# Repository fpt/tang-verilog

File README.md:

# tang-verilog

Tang Nano 20K (Gowin GW2AR-18) と RP2350 で、レトロゲーム機の VDP のようなものを作るためのプロジェクトです。

- FPGA 側 (Tang Nano 20K): VDP 本体。今は HDMI (DVI) に 640x480@60Hz の映像を出す
- RP2350 側: ホスト CPU 役。SPI などで VDP にコマンドを送る (予定)

ツールはすべてオープンソースのものを Docker コンテナ内で動かします。ホストに必要なのは Docker と make だけです
(ボードへの書き込みだけは例外です。下の「書き込み」を参照)。

## ドキュメント

- [docs/SPECIFICATION.md](docs/SPECIFICATION.md): アプリケーション開発者向けの仕様 (接続、レジスタ、コマンド、データ形式、タイミング、制限)
- [docs/ARCHITECTURE.md](docs/ARCHITECTURE.md): 設計方針と今の実装 (レジスタバス、レジスタマップ、クロック、SDRAM)
- [docs/GPU_PLAN.md](docs/GPU_PLAN.md): SDRAM フレームバッファの tiny-GPU の開発計画 (ハーネスで検証しながら進める)
- [docs/WIRING.md](docs/WIRING.md): RP2350 と Tang Nano 20K の配線・SPI ピン割り当て
- [docs/DEVELOPMENT.md](docs/DEVELOPMENT.md): 開発環境の補足

## 状態

- 実機 (Tang Nano 20K + HDMI) で、SPI のハーネス (RP2040-Zero) からコマンド GPU (図形・BLIT)、ライン合成、タイル レイヤが動いている。
  すべて 参照モデル = Verilator = 実機 の CRC で確かめている ([docs/HARNESS.md](docs/HARNESS.md))
- 進み具合: コマンド GPU は [docs/GPU_PLAN.md](docs/GPU_PLAN.md) (M0〜M9 済み、M8 はやめた)、エミュレータ向けのタイル/スプライト エンジンは
  [docs/EMU_GPU_PLAN.md](docs/EMU_GPU_PLAN.md) (E1〜E4・E7 (Mode 7 と霧) 済み、次は E5 のホスト翻訳層)、
  [rs-kessel](https://github.com/fpt/rs-kessel) を載せる準備は [docs/KESSEL_ON_VDP.md](docs/KESSEL_ON_VDP.md) (K1〜K4 の VDP 側 = 8bpp の面・BLIT4・スプライトのセル順とバンク・STRETCH_BLIT・ライトマップ済み)
- 3D GPU (タイルベース、VDP を外した別のビットストリーム `make bitstream-gpu3d`。フラッシュに VDP と一緒に置き、`RECONFIG` で入れ替える) は [docs/GPU3D_PLAN.md](docs/GPU3D_PLAN.md) (G0 の骨格、G1 の三角形 (単色・Gouraud・Z)、G2 のタイルベースの遅延描画 (TBDR)、G3 のテクスチャ、G4 の半透明、G5 の場面 (ロゴ・トンネル・映り込む玉の部屋・夜の街、`harness.py demo <場面>`) 済み)
- 本番ホスト (RP2350) とのリンクは HSTX に決めた (EMU_GPU_PLAN.md の「本番のリンク」)。まだ作っていない

## ツール

| 用途 | ツール | 入手元 |
| --- | --- | --- |
| 論理合成 | Yosys + yosys-slang プラグイン (SystemVerilog フロントエンド) | [OSS CAD Suite](https://github.com/YosysHQ/oss-cad-suite-build) |
| 配置配線 | nextpnr-himbaechel (Gowin) | 同上 |
| ビットストリーム生成 | apicula (`gowin_pack`) | 同上 |
| シミュレーション | Icarus Verilog / Verilator / cocotb | 同上 |
| 書き込み | openFPGALoader | 同上 (ただしコンテナからは USB が使えない) |
| RP2350 ファームウェア | arm-none-eabi-gcc + pico-sdk 2.3.1 + picotool | Debian パッケージ / GitHub |

## セットアップ

```bash
make images
```

`docker/fpga` と `docker/pico` の 2 つのイメージを順番にビルドします (`make image-fpga` / `make image-pico` で個別にも可)。
FPGA 側は OSS CAD Suite (約 1GB) をダウンロードするので時間がかかります。
開発環境についての補足は [docs/DEVELOPMENT.md](docs/DEVELOPMENT.md) を参照してください。

### メモリについて

Docker Desktop の割り当てメモリが少ないと、イメージのビルド (特に picotool のコンパイル) でメモリが足りなくなることがあります。
2 つのイメージは並列ではなく 1 つずつビルドしてください。

## 使い方

```bash
make help
```

| コマンド | 内容 |
| --- | --- |
| `make lint` | Verilator で RTL を lint |
| `make sim` | `sim/tb_*.sv` を全部実行 (`SIM=verilator` で Verilator を使う)。VCD は `build/sim/` に出力 |
| `make sim-tb_tmds_encoder` | テストベンチを 1 つだけ実行 |
| `make render` | Verilator で映像出力を回し、各フレームを `build/render/frame_*.png` に保存 |
| `make bitstream` | 合成 → 配置配線 → VDP (`build/vdp/top.fs`) と 3D GPU (`build/gpu3d/top.fs`)。1 つだけなら `make bitstream-vdp` / `bitstream-gpu3d` |
| `make flash` | VDP をフラッシュの 0x000000、3D GPU を 0x100000 に (電源を入れると VDP。`harness.py reconfig` か、要るときに `harness.py` が自分で入れ替える) |
| `make prog` / `make prog-3d` | VDP / 3D GPU を SRAM に (開発中の確かめ) |
| `make bitstream-lcd` | 40 ピン RGB LCD (800x480) に HDMI と同じテストパターンを出す → `build/lcd/top_lcd.fs` (`make prog-lcd` で書き込み) |
| `make scenario SCENARIO=scenarios/m5_basic.json` | GPU のシナリオをシステム全体の RTL (Verilator) で走らせ、参照モデルの CRC と比べる。実機は `harness.py scenario` |
| `make render FREEZE=1` | アニメーションを止めた参照画像と各フレームの CRC (`frames.json`) を `build/render_frozen/` に (実機の `FRAME_CRC` と比べる) |
| `make render-lcd` | LCD 版の映像を `build/render_lcd/frame_*.png` に保存 |
| `make harness-fw` / `python3 tools/harness/harness.py <cmd>` | ハーネスの RP2 ブリッジとホストツール (`status` / `selftest` / `memtest` / `frametest` / `fbtest` / `prog` など)。詳細は [docs/HARNESS.md](docs/HARNESS.md) |
| `make prog` / `make flash` | Tang Nano 20K の SRAM / Flash に書き込み (書く前に、ハーネスのピンと衝突しないかを `pincheck-<設計>` が自動で検査する) |
| `make fw` | RP2350 ファームウェアをビルド (`firmware/build/vdp_host.uf2`) |
| `make shell` / `make shell-pico` | 各コンテナのシェルに入る |
| `make zip` | 別環境へ持っていくためのソース一式を `dist/<ディレクトリ名>.zip` に作成 (ホストの git と zip を使用) |

### 波形を見る

GTKWave は GUI ツールなので、macOS 上の Docker からは簡単には開けません。ローカルに何も入れずに見るなら
[Surfer のブラウザ版](https://app.surfer-project.org/) で `build/sim/*.vcd` を開いてください。

### 書き込み

macOS 上の Docker Desktop のコンテナからは USB デバイスにアクセスできないため、`make prog` だけはホストの `openFPGALoader` を使います。

```bash
brew install openfpgaloader
```

ホストに何も入れたくない場合は、Gowin 公式の Programmer を使う方法もあります。

RP2350 は BOOTSEL ボタンを押しながら USB 接続し、出てきたドライブに `firmware/build/vdp_host.uf2` をコピーすれば書き込めます (ツール不要)。
ボードを変えるときは `make fw PICO_BOARD=<ボード名>`、RISC-V コア (Hazard3) を使うときは `make fw PICO_PLATFORM=rp2350-riscv` です。

## ディレクトリ構成

```
docker/
  fpga/Dockerfile        FPGA ツール (OSS CAD Suite)
  pico/Dockerfile        RP2350 ツール (pico-sdk, picotool)
rtl/
  vdp/                   ベンダ非依存の RTL (シミュレーション可能)
    video_timing.sv      640x480@60Hz のタイミング生成
    vdp_core.sv          VDP コアの雛形 (カラーバー + 市松模様 + 跳ね回る四角)
    tmds_encoder.sv      DVI の TMDS エンコーダ
    vdp_video.sv         タイミング + コアをまとめたもの (MODE 0: 640x480 HDMI / 1: 800x480 LCD)
  gowin/                 Gowin のプリミティブを使う部分
    dvi_tx.sv            OSER10 + TLVDS_OBUF による DVI 送信
    top.sv               トップ (rPLL 126MHz → CLKDIV /5 → 25.2MHz)
    top_lcd.sv           RGB LCD 版トップ (rPLL 33MHz、800x480)
    blackbox/            Gowin プリミティブのブラックボックス定義 (合成専用)
constraints/
  tangnano20k.cst        ピン配置 (HDMI)
  tangnano20k_lcd.cst    ピン配置 (40 ピン RGB LCD)
sim/
  tb_*.sv                テストベンチ (Icarus Verilog / Verilator)
  verilator/render_main.cpp  フレームを画像に書き出すシミュレータ
firmware/                RP2350 ファームウェア (pico-sdk)
scripts/
  ppm2png.py             PPM → PNG 変換
```

## ハードウェアメモ (Tang Nano 20K)

| 信号 | ピン |
| --- | --- |
| 27MHz クロック | 4 |
| ボタン S1 / S2 (押下で 1) | 88 / 87 |
| LED0〜5 (負論理) | 15〜20 |
| HDMI CLK / D0 / D1 / D2 (P,N) | 33,34 / 35,36 / 37,38 / 39,40 |

- デバイス: `GW2AR-LV18QN88C8/I7` (nextpnr の family は `GW2A-18C`)
- 40 ピン RGB LCD の R/G 信号の一部 (33〜40) は HDMI と同じピンなので、HDMI と LCD は同時には使えません (別の `TARGET`)
- ピクセルクロックは 25.2MHz で、規格値の 25.175MHz からわずかにずれています (たいていのモニタは問題なく表示します)

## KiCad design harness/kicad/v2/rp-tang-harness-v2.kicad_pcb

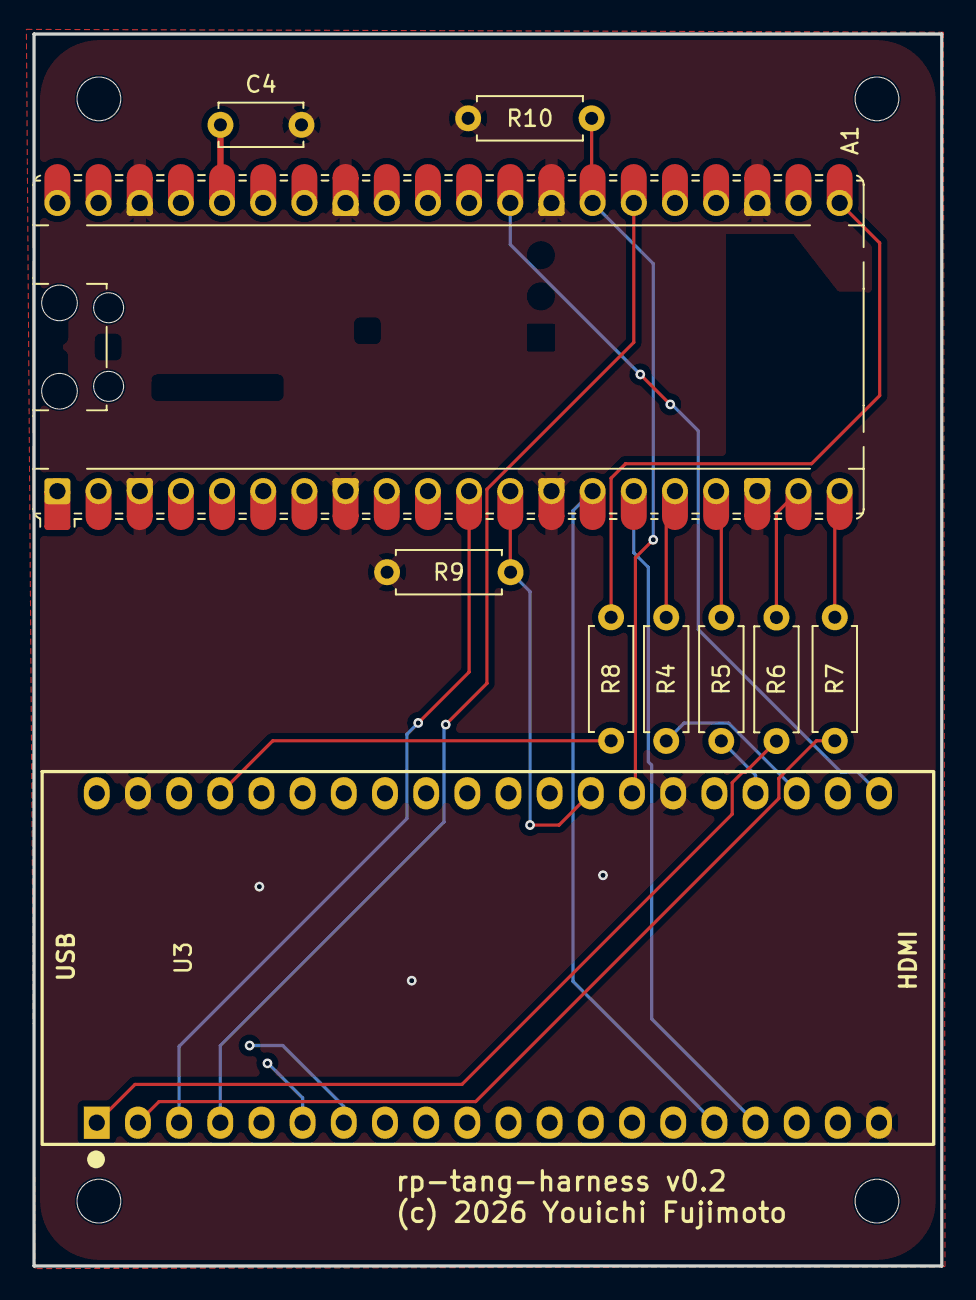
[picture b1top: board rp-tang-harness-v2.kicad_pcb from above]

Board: 2 copper layers, 56.0 x 76.0 mm, 14 parts (0 on the bottom side), 19 nets.

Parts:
A1: RaspberryPi_Pico; RaspberryPi_Pico_Common_Unspecified
C4: 0.1u; C_Disc_D5.0mm_W2.5mm_P5.00mm
H_LL1: MountingHole; MountingHole_2.7mm
H_LR1: MountingHole; MountingHole_2.7mm
H_UL1: MountingHole; MountingHole_2.7mm
H_UR1: MountingHole; MountingHole_2.7mm
R4, R5, R6, R7, R8: 33; R_Axial_DIN0207_L6.3mm_D2.5mm_P7.62mm_Horizontal
R9, R10: 4.7k; R_Axial_DIN0207_L6.3mm_D2.5mm_P7.62mm_Horizontal
U3: Sipeed_Tang_Nano_20K; DIP-40_TangNano20K

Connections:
+3V3: A1.36 (3V3), C4.1
/CIPO: A1.11 (GPIO8), U3.3 (75_IOT34A)
/COPI: A1.15 (GPIO11), U3.17 (19_IOL51A)
/CS: A1.12 (GPIO9), R9.1, U3.28 (86_IOT4A)
/HSTX_CLK: R8.2, U3.37 (80_IOT27A)
/HSTX_CLK_P: A1.21 (GPIO16), R8.1
/HSTX_D0: R4.2, U3.23 (71_IOT44A)
/HSTX_D0_P: A1.16 (GPIO12), R4.1
/HSTX_D1: R5.2, U3.24 (72_IOT40B)
/HSTX_D1_P: A1.17 (GPIO13), R5.1
/HSTX_D2: R6.2, U3.1 (73_IOT40A)
/HSTX_D2_P: A1.19 (GPIO14), R6.1
/HSTX_D3: R7.2, U3.2 (74_IOT34B)
/HSTX_D3_P: A1.20 (GPIO15), R7.1
/IRQ: A1.26 (GPIO20), U3.4 (85_IOT4B)
/RESET: A1.27 (GPIO21), R10.1, U3.27 (79_IOT27B)
/SCK: A1.14 (GPIO10), U3.16 (20_IOL51B)
/VSYNC: A1.29 (GPIO22), U3.21 (52_IOR39A)
GND: A1.3 (GND), A1.8 (GND), A1.13 (GND), A1.18 (GND), A1.23 (GND), A1.28 (GND), A1.33 (AGND), A1.38 (GND), C4.2, R9.2, R10.2, U3.20 (GND), U3.26 (GND), U3.39 (GND)

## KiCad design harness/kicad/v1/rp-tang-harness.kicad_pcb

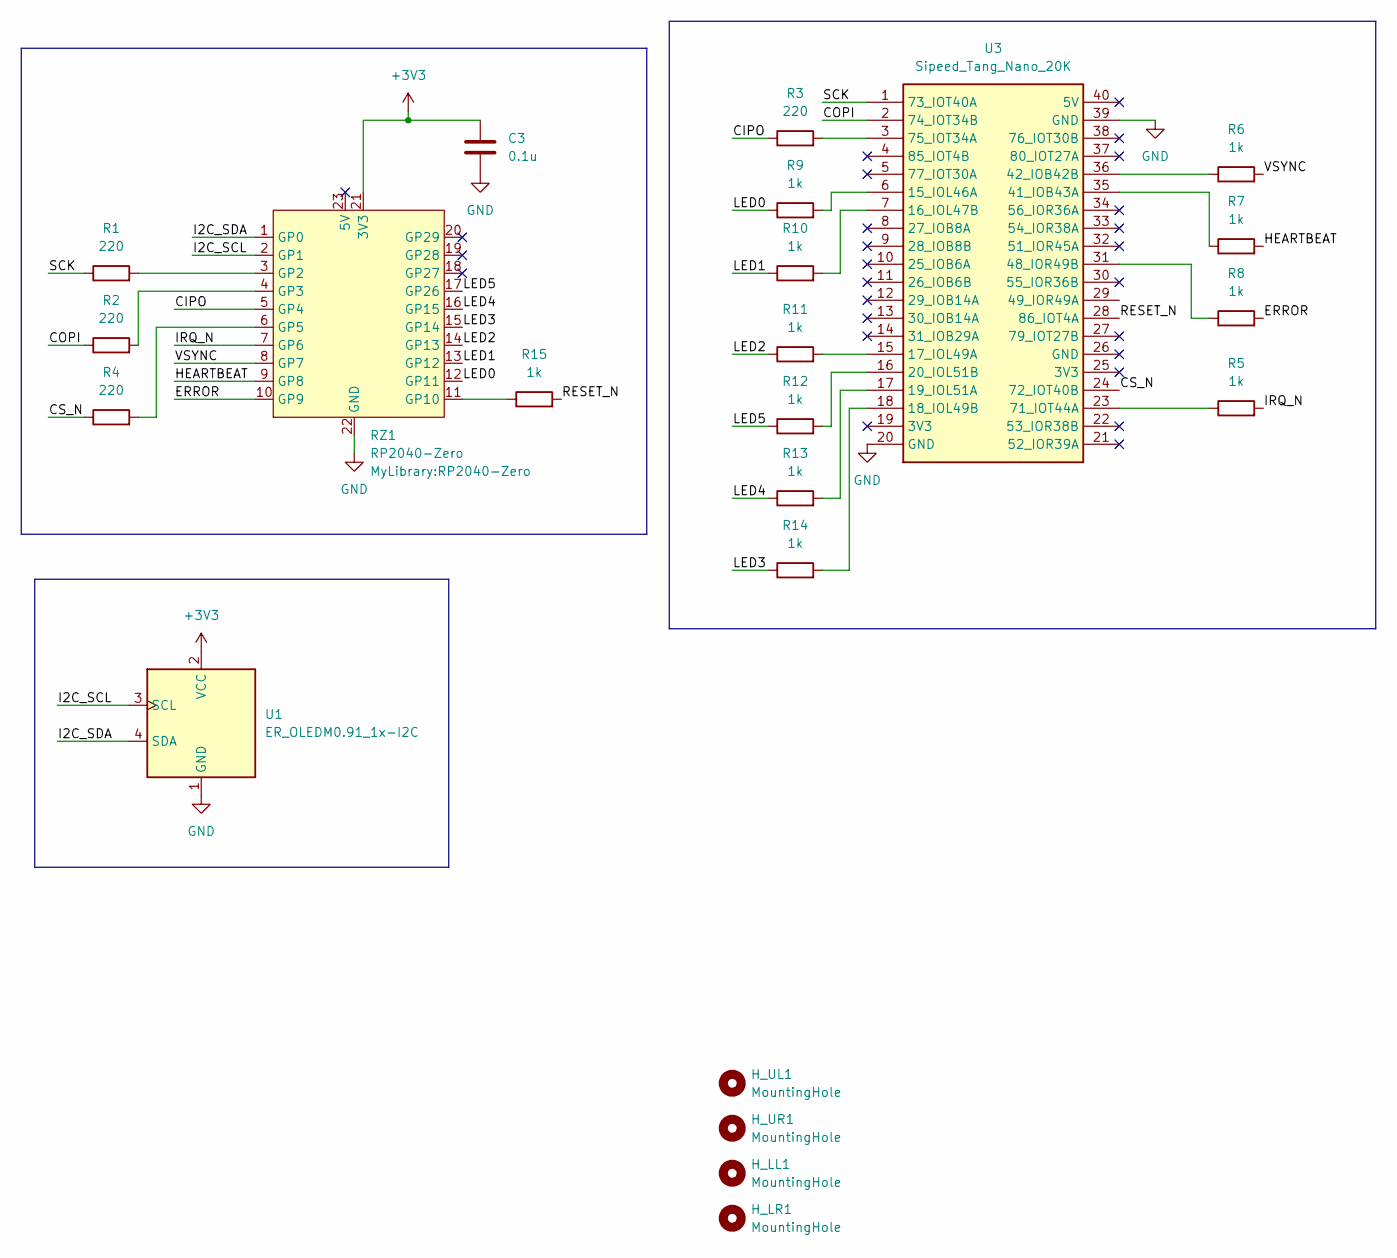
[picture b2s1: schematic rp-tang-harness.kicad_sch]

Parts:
C3: 0.1u; C_Disc_D5.0mm_W2.5mm_P5.00mm
H_LL1: MountingHole; MountingHole_2.7mm
H_LR1: MountingHole; MountingHole_2.7mm
H_UL1: MountingHole; MountingHole_2.7mm
H_UR1: MountingHole; MountingHole_2.7mm
R1, R2, R3, R4: 220; R_Axial_DIN0207_L6.3mm_D2.5mm_P7.62mm_Horizontal
R5, R6, R7, R8, R9, R10, R11, R12, R13, R14, R15: 1k; R_Axial_DIN0207_L6.3mm_D2.5mm_P7.62mm_Horizontal
RZ1: RP2040-Zero
U1: ER_OLEDM0.91_1x-I2C; SSD1306 OLED 096 I2C
U3: Sipeed_Tang_Nano_20K; DIP-40_TangNano20K

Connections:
+3V3: C3.1, RZ1.21 (3V3), U1.2 (VCC)
/CIPO: R3.1, RZ1.5 (GP4)
/COPI: R2.1, U3.2 (74_IOT34B)
/CS_N: R4.1, U3.24 (72_IOT40B)
/ERROR: R8.2, RZ1.10 (GP9)
/HEARTBEAT: R7.2, RZ1.9 (GP8)
/I2C_SCL: RZ1.2 (GP1), U1.3 (SCL)
/I2C_SDA: RZ1.1 (GP0), U1.4 (SDA)
/IRQ_N: R5.2, RZ1.7 (GP6)
/LED0: R9.1, RZ1.12 (GP11)
/LED1: R10.1, RZ1.13 (GP12)
/LED2: R11.1, RZ1.14 (GP13)
/LED3: R14.1, RZ1.15 (GP14)
/LED4: R13.1, RZ1.16 (GP15)
/LED5: R12.1, RZ1.17 (GP26)
/RESET_N: R15.2, U3.28 (86_IOT4A)
/SCK: R1.1, U3.1 (73_IOT40A)
/VSYNC: R6.2, RZ1.8 (GP7)
GND: C3.2, RZ1.22 (GND), U1.1 (GND), U3.20 (GND), U3.39 (GND)
unnamed: R1.2, RZ1.3 (GP2)
unnamed: R2.2, RZ1.4 (GP3)
unnamed: R4.2, RZ1.6 (GP5)
unnamed: R15.1, RZ1.11 (GP10)
unnamed: R9.2, U3.6 (15_IOL46A)
unnamed: R10.2, U3.7 (16_IOL47B)
unnamed: R11.2, U3.15 (17_IOL49A)
unnamed: R14.2, U3.18 (18_IOL49B)
unnamed: R13.2, U3.17 (19_IOL51A)
unnamed: R12.2, U3.16 (20_IOL51B)
unnamed: R7.1, U3.35 (41_IOB43A)
unnamed: R6.1, U3.36 (42_IOB42B)
unnamed: R8.1, U3.31 (48_IOR49B)
unnamed: R5.1, U3.23 (71_IOT44A)
unnamed: R3.2, U3.3 (75_IOT34A)

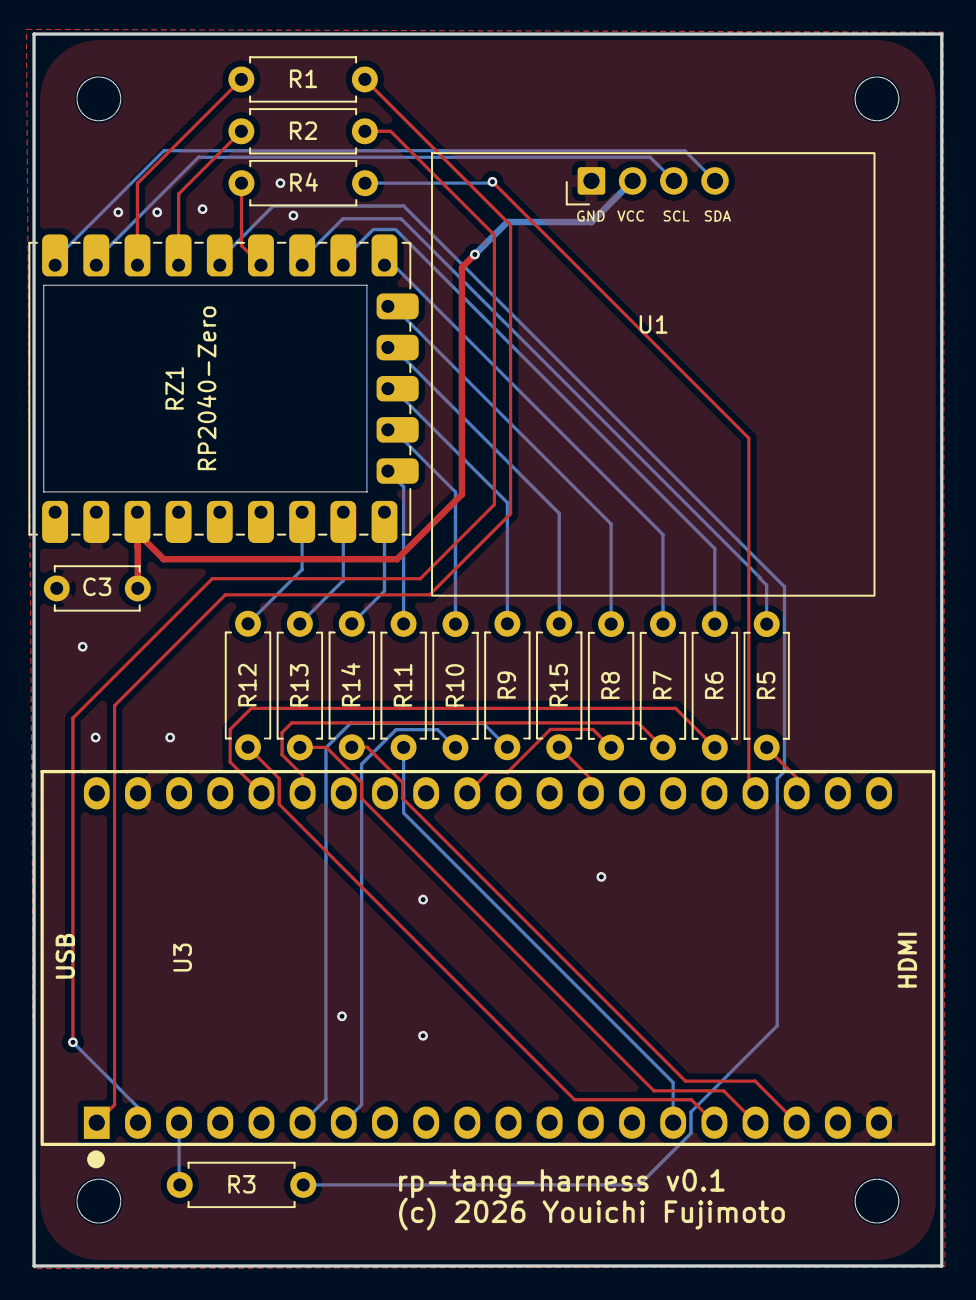
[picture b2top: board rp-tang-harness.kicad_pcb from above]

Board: 2 copper layers, 56.0 x 76.0 mm, 23 parts (0 on the bottom side), 34 nets.

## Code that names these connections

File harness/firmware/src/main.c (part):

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
static void gpio_cb(uint gpio, uint32_t events) {
    if (!(events & GPIO_IRQ_EDGE_RISE)) return;
    edge_t *e = gpio == PIN_HEARTBEAT ? &edge_hb : gpio == PIN_VSYNC ? &edge_vs : gpio == PIN_IRQ ? &edge_irq : NULL;
    if (!e) return;
    uint64_t now = time_us_64();
    if (e->last_us) e->period_us = (uint32_t)(now - e->last_us);
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}

static void monitor_enable(void) {
    gpio_set_irq_enabled_with_callback(PIN_HEARTBEAT, GPIO_IRQ_EDGE_RISE, true, gpio_cb);
    gpio_set_irq_enabled(PIN_VSYNC, GPIO_IRQ_EDGE_RISE, true);
    gpio_set_irq_enabled(PIN_IRQ, GPIO_IRQ_EDGE_RISE, true);
}

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    gpio_put(PIN_CS, 0);
    gpio_set_dir(PIN_CS, GPIO_OUT);
    gpio_set_function(PIN_SCK, GPIO_FUNC_SPI);
    gpio_set_function(PIN_COPI, GPIO_FUNC_SPI);
    gpio_set_function(PIN_CIPO, GPIO_FUNC_SPI);
    gpio_put(PIN_CS, 1);
    spi_write_read_blocking(BRIDGE_SPI, tx, rx, n);
    gpio_put(PIN_CS, 0);
    release(PIN_SCK);
    release(PIN_COPI);
    release(PIN_CIPO);
    release(PIN_CS);
}

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
// FPGA -> RP2 の各線が使うカウンタのビット (rtl/gowin/top_harness_probe.sv と合わせる)
static const struct { unsigned gpio; int bit; } PROBE_BITS[] = {
    {PIN_CIPO, 10}, {PIN_IRQ, 11}, {PIN_VSYNC, 12}, {PIN_HEARTBEAT, 13}, {PIN_ERROR, 14},
    {PIN_LED0, 15}, {PIN_LED1, 16}, {PIN_LED2, 17}, {PIN_LED3, 18}, {PIN_LED4, 19}, {PIN_LED5, 20},
};

// RP2 が High にする線と、FPGA が折り返してくる線
static const struct { unsigned drive; unsigned echo; } LOOPBACK[] = {
    {PIN_SCK, PIN_CIPO}, {PIN_COPI, PIN_IRQ}, {PIN_CS, PIN_VSYNC}, {PIN_RESET, PIN_HEARTBEAT},
};

static void cmd_wiretest(void) {
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    gpio_put(PIN_CS, 0);
    gpio_set_dir(PIN_CS, GPIO_OUT);
    gpio_set_function(PIN_SCK, GPIO_FUNC_SPI);
    gpio_set_function(PIN_COPI, GPIO_FUNC_SPI);
    gpio_set_function(PIN_CIPO, GPIO_FUNC_SPI);
}

static void spi_pins_off(void) {
    release(PIN_SCK);
    release(PIN_COPI);
    release(PIN_CIPO);
    release(PIN_CS);
}

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

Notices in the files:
harness/kicad/v1/rp-tang-harness.kicad_pcb:
(c) 2026 Youichi Fujimoto
